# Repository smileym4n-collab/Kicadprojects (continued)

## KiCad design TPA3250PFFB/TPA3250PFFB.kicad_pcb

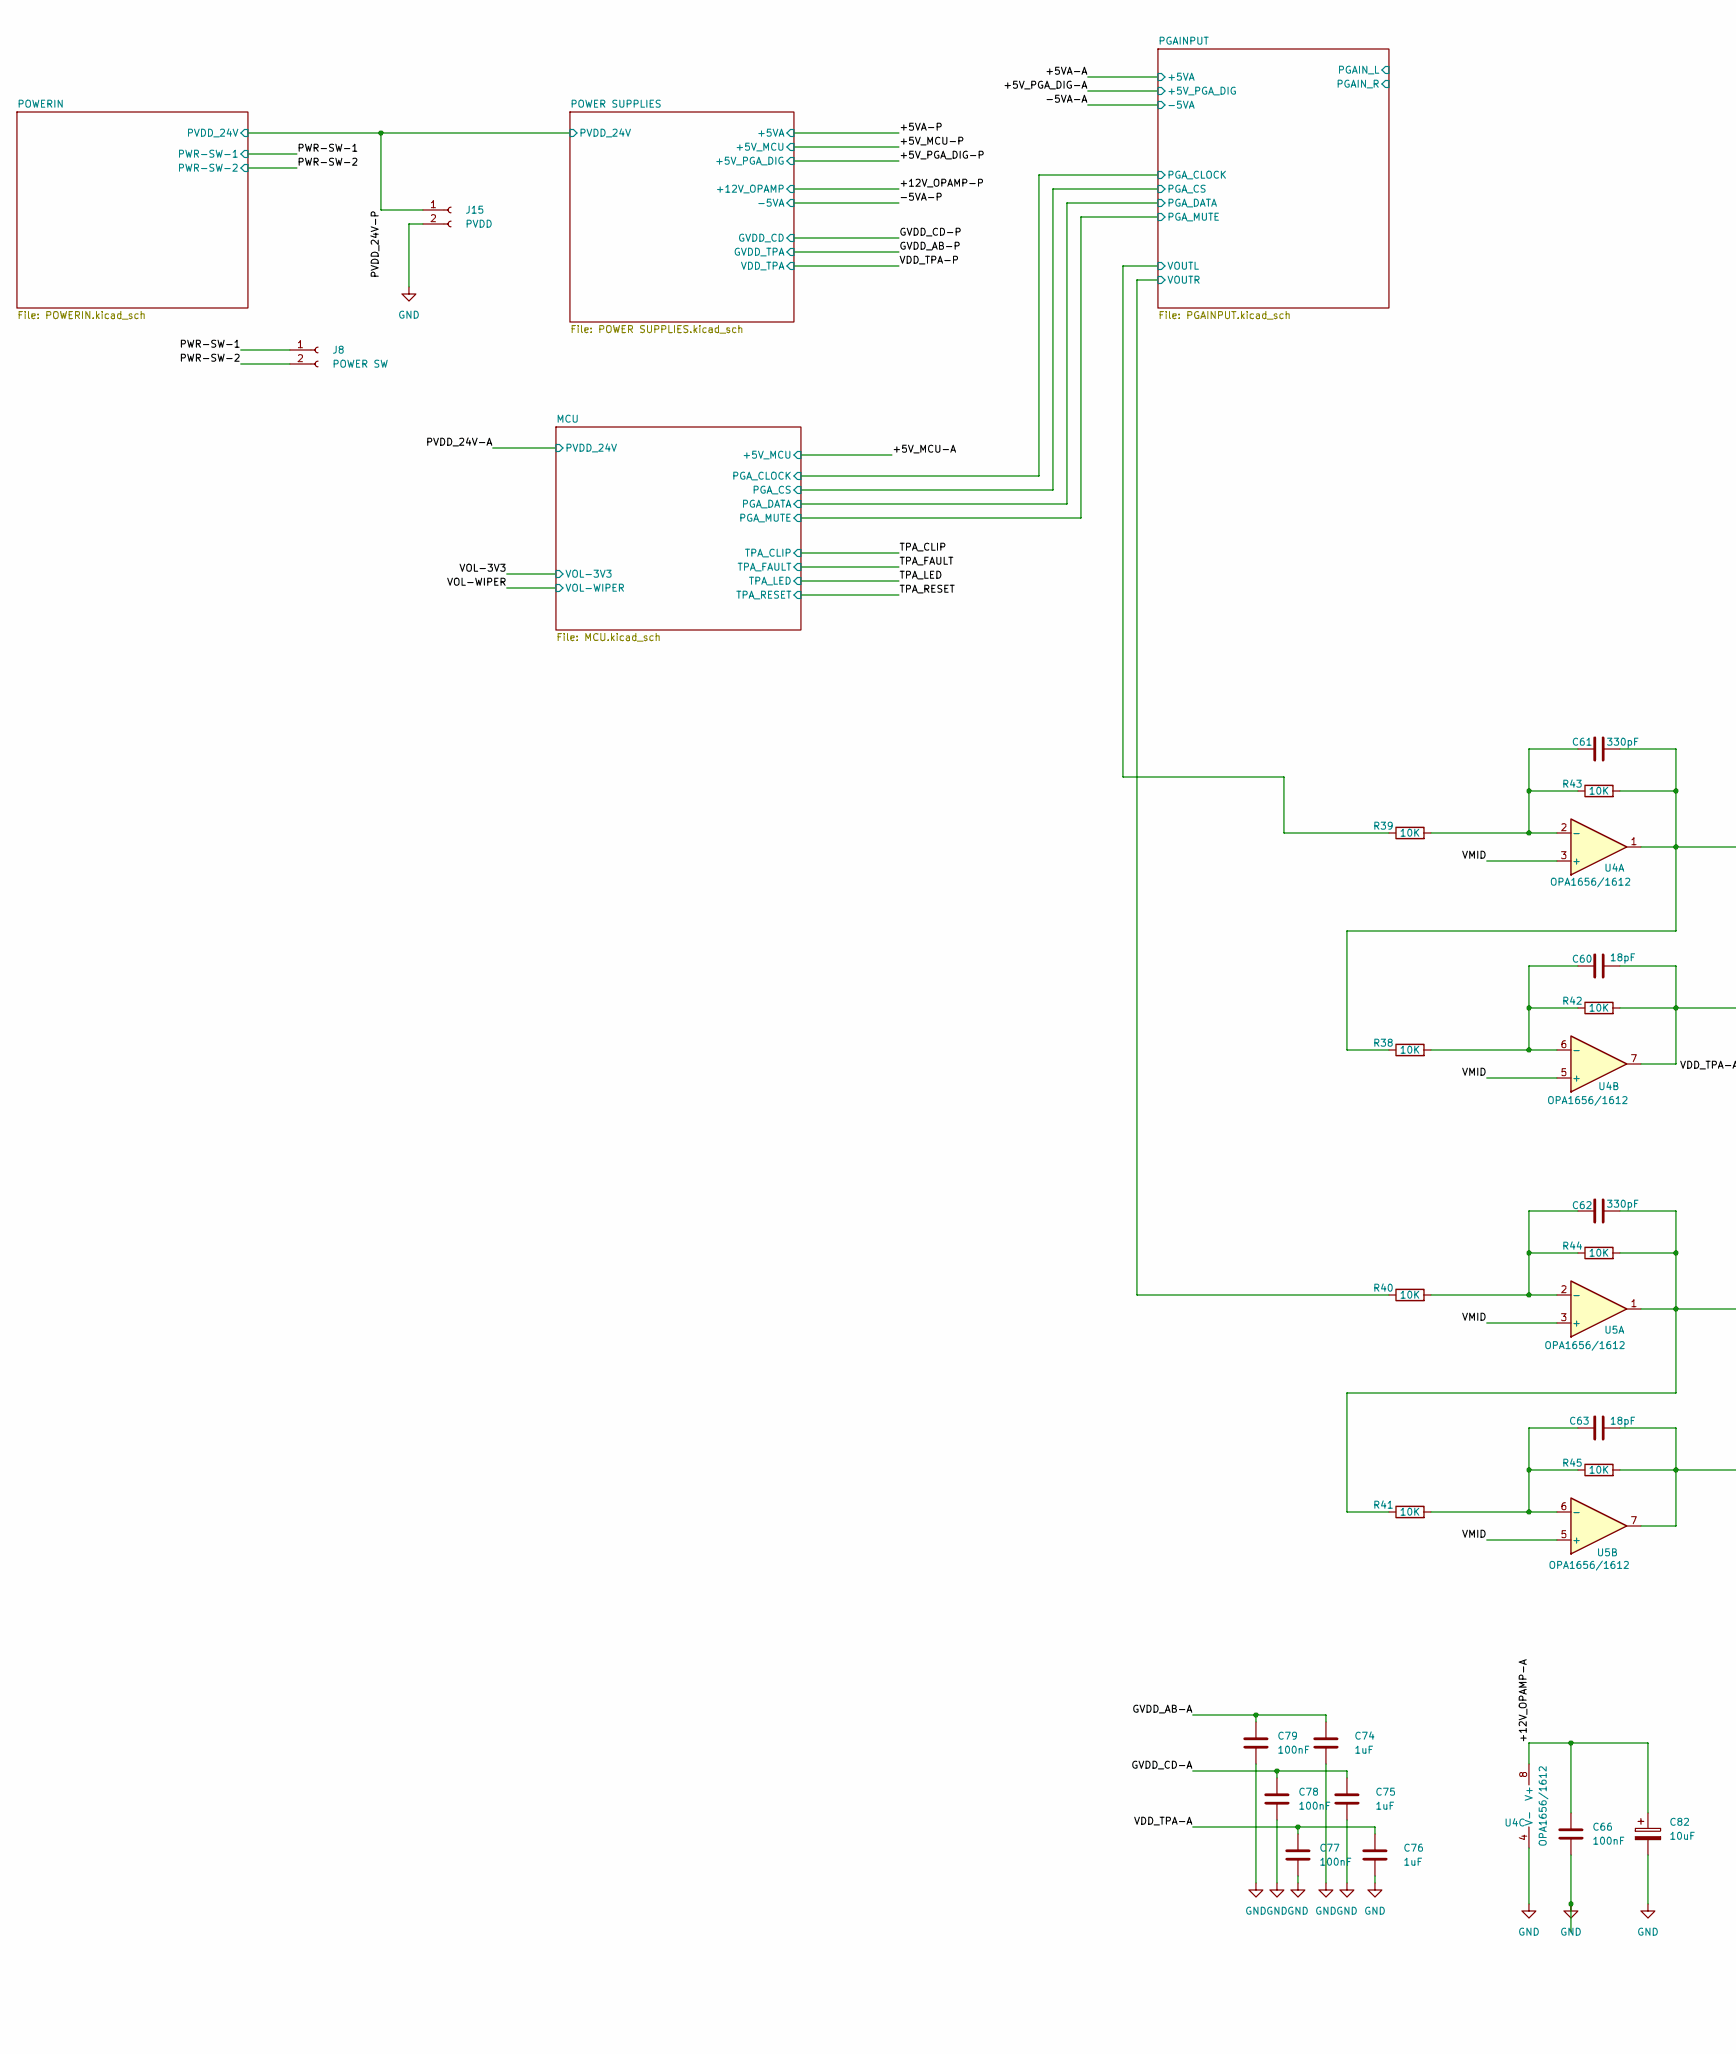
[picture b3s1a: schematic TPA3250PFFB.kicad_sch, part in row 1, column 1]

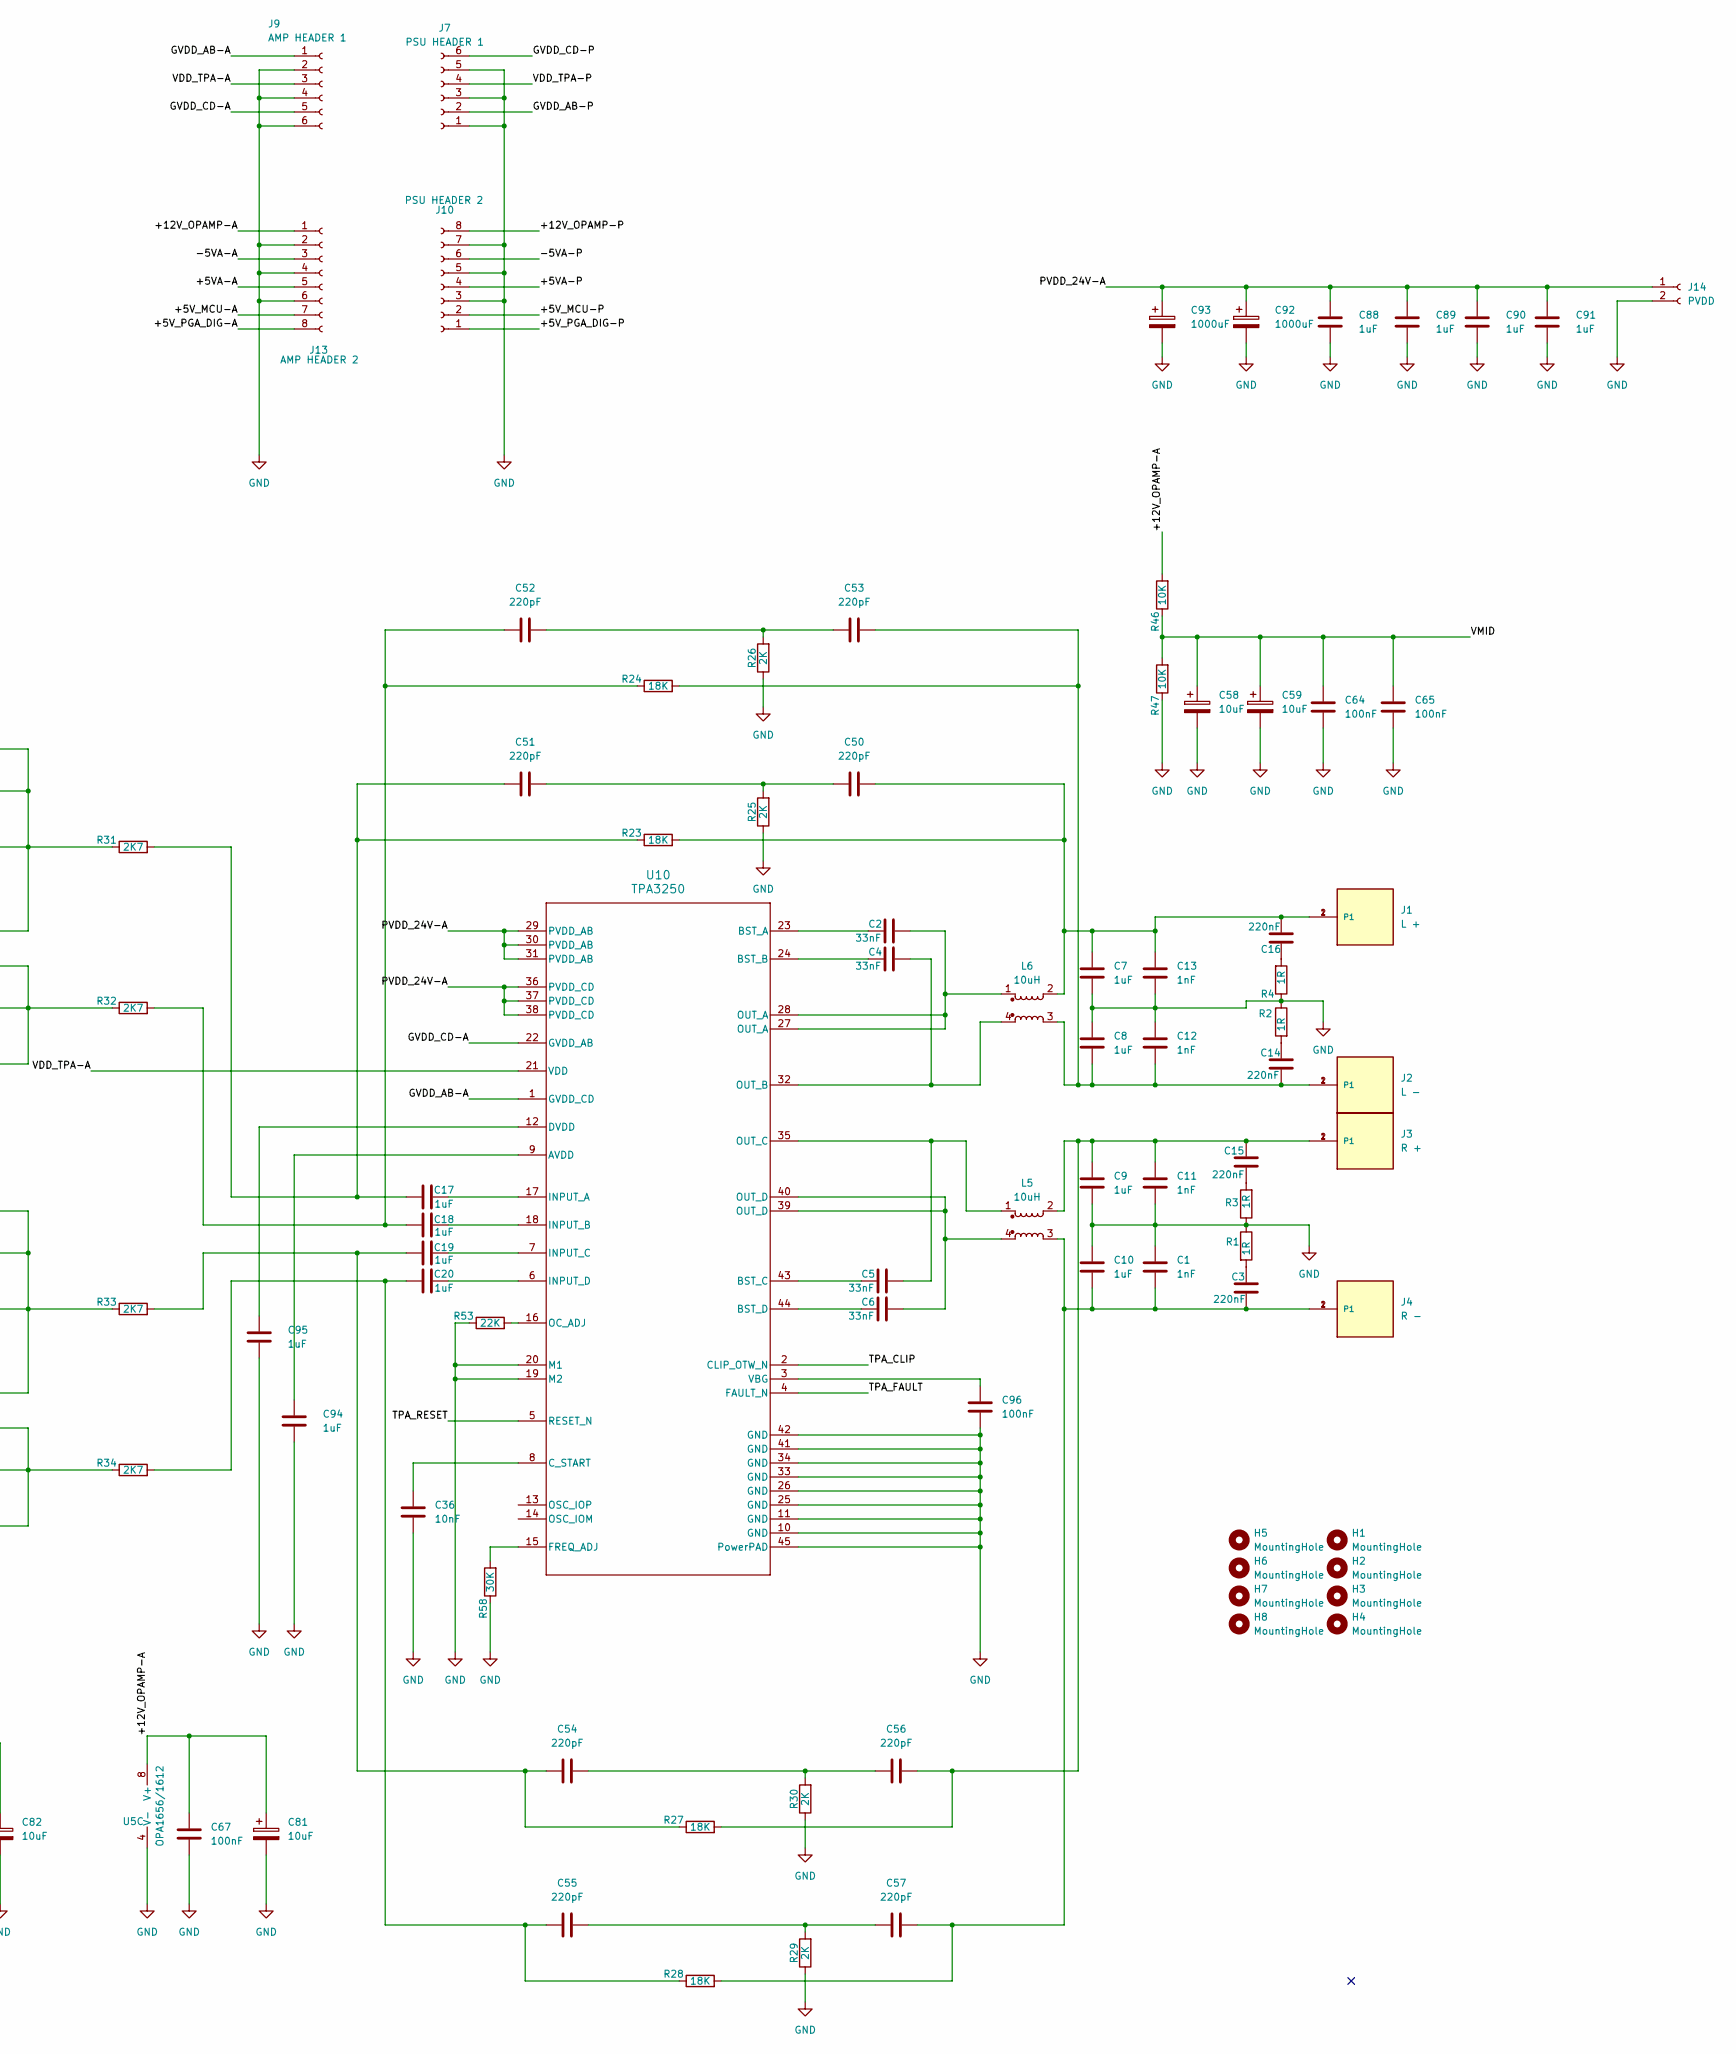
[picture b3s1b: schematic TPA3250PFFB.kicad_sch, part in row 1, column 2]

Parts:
C1, C11, C12, C13: 1nF; C_0805_2012Metric_Pad1.18x1.45mm_HandSolder
C2, C4, C5, C6: 33nF; C_0805_2012Metric_Pad1.18x1.45mm_HandSolder
C3, C14, C15, C16: 220nF; C_1206_3216Metric_Pad1.33x1.80mm_HandSolder
C7, C8, C9, C10: 1uF; C_Rect_L18.0mm_W8.0mm_P15.00mm_FKS3_FKP3
C17, C18, C19, C20: 1uF; C_Rect_L7.2mm_W5.5mm_P5.00mm_FKS2_FKP2_MKS2_MKP2
C36: 10nF; C_0805_2012Metric_Pad1.18x1.45mm_HandSolder
C50, C51, C52, C53, C54, C55, C56, C57: 220pF; C_0805_2012Metric_Pad1.18x1.45mm_HandSolder
C58, C59, C81, C82: 10uF; CP_Radial_D4.0mm_P2.00mm
C60, C63: 18pF; C_0603_1608Metric_Pad1.08x0.95mm_HandSolder
C61, C62: 330pF; C_0805_2012Metric_Pad1.18x1.45mm_HandSolder
C64, C65, C66, C67, C77, C78, C79, C96: 100nF; C_1206_3216Metric_Pad1.33x1.80mm_HandSolder
C74, C75, C76, C88, C89, C90, C91, C94, C95: 1uF; C_1206_3216Metric_Pad1.33x1.80mm_HandSolder
C92, C93: 1000uF; CP_Radial_D12.5mm_P5.00mm
H1, H2, H3, H4, H5, H6, H7, H8: MountingHole; MountingHole_4.3mm_M4
J1: L +; PART_DESCRIPTION CONN QC TAB 0.250 SOLDER
J2: L -; PART_DESCRIPTION CONN QC TAB 0.250 SOLDER
J3: R +; PART_DESCRIPTION CONN QC TAB 0.250 SOLDER
J4: R -; PART_DESCRIPTION CONN QC TAB 0.250 SOLDER
J7: PSU HEADER 1; JST_XH_B6B-XH-A_1x06_P2.50mm_Vertical
J8: POWER SW; JST_XH_B2B-XH-A_1x02_P2.50mm_Vertical
J9: AMP HEADER 1; JST_XH_B6B-XH-A_1x06_P2.50mm_Vertical
J10: PSU HEADER 2; JST_XH_B8B-XH-A_1x08_P2.50mm_Vertical
J13: AMP HEADER 2; JST_XH_B8B-XH-A_1x08_P2.50mm_Vertical
J14, J15: PVDD; Molex_KK-396_A-41791-0002_1x02_P3.96mm_Vertical
L5, L6: 10uH; CSAD0660-100M
R1, R2, R3, R4: 1R; R_2512_6332Metric_Pad1.40x3.35mm_HandSolder
R23, R24, R27, R28: 18K; R_0805_2012Metric_Pad1.20x1.40mm_HandSolder
R25, R26, R29, R30: 2K; R_0805_2012Metric_Pad1.20x1.40mm_HandSolder
R31, R32, R33, R34: 2K7; R_0805_2012Metric_Pad1.20x1.40mm_HandSolder
R38, R39, R40, R41, R42, R43, R44, R45, R46, R47: 10K; R_0805_2012Metric_Pad1.20x1.40mm_HandSolder
R53: 22K; R_0805_2012Metric_Pad1.20x1.40mm_HandSolder
R58: 30K; R_0805_2012Metric_Pad1.20x1.40mm_HandSolder
U4, U5: OPA1656/1612; SOIC-8_3.9x4.9mm_P1.27mm
U10: TPA3250

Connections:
/+5VA-A: J13.5; also elsewhere on the board
/+5VA-P: J10.4; also elsewhere on the board
/+5V_MCU-A: J13.7; also elsewhere on the board
/+5V_MCU-P: J10.2; also elsewhere on the board
/+5V_PGA_DIG-A: J13.8; also elsewhere on the board
/+5V_PGA_DIG-P: J10.1; also elsewhere on the board
/+12V_OPAMP-A: C66.1, C67.1, C81.1, C82.1, J13.1, R46.2, U4.8 (V+), U5.8 (V+)
/+12V_OPAMP-P: J10.8; also elsewhere on the board
/-5VA-A: J13.3; also elsewhere on the board
/GVDD_AB-A: C74.1, C79.1, J9.1, U10.1 (GVDD_CD)
/GVDD_AB-P: J7.2; also elsewhere on the board
/GVDD_CD-A: C75.1, C78.1, J9.5, U10.22 (GVDD_AB)
/GVDD_CD-P: J7.6; also elsewhere on the board
/PGAINPUT/VOUTL: R39.1; also elsewhere on the board
/PGAINPUT/VOUTR: R40.1; also elsewhere on the board
/PVDD_24V-A: C88.1, C89.1, C90.1, C91.1, C92.1, C93.1, J14.1, U10.29 (PVDD_AB), U10.30 (PVDD_AB), U10.31 (PVDD_AB), U10.36 (PVDD_CD), U10.37 (PVDD_CD), U10.38 (PVDD_CD); also elsewhere on the board
/PVDD_24V-P: J15.1; also elsewhere on the board
/PWR-SW-1: J8.1; also elsewhere on the board
/TPA_CLIP: U10.2 (CLIP_OTW_N); also elsewhere on the board
/TPA_FAULT: U10.4 (FAULT_N); also elsewhere on the board
/TPA_RESET: U10.5 (RESET_N); also elsewhere on the board
/VDD_TPA-A: C76.1, C77.1, J9.3, U10.21 (VDD)
/VDD_TPA-P: J7.4; also elsewhere on the board
/VMID: C58.1, C59.1, C64.1, C65.1, R46.1, R47.2, U4.3 (+), U4.5 (+), U5.3 (+), U5.5 (+)
unnamed: C2.2, L6.1, U10.27 (OUT_A), U10.28 (OUT_A)
unnamed: C3.1, R1.2
unnamed: C6.2, L5.4, U10.39 (OUT_D), U10.40 (OUT_D)
unnamed: C14.1, R2.2
unnamed: C15.1, R3.2
unnamed: C16.1, R4.2
unnamed: C17.1, C51.1, R23.1, R31.2
unnamed: C18.1, C52.1, R24.1, R32.2
unnamed: C19.1, C54.1, R27.1, R33.2
unnamed: C20.1, C55.1, R28.1, R34.2
unnamed: C50.1, C51.2, R25.2
unnamed: C52.2, C53.1, R26.2
unnamed: C54.2, C56.1, R30.2
unnamed: C55.2, C57.1, R29.2
unnamed: C60.2, R32.1, R42.2, U4.7
unnamed: C61.2, R31.1, R38.1, R43.2, U4.1
unnamed: C62.2, R33.1, R41.1, R44.2, U5.1
unnamed: C63.2, R34.1, R45.2, U5.7
unnamed 66: C7.2, C13.1, C16.2, C50.2, J1.1, J1.2, L6.2, R23.2; also elsewhere on the board
unnamed 67: C8.1, C12.2, C14.2, C53.2, J2.1, J2.2, L6.3, R24.2; also elsewhere on the board
unnamed 68: C9.2, C11.1, C15.2, C56.2, J3.1, J3.2, L5.2, R27.2; also elsewhere on the board
unnamed 69: C1.2, C3.2, C10.1, C57.2, J4.1, J4.2, L5.3, R28.2; also elsewhere on the board
unnamed: C61.1, R39.2, R43.1, U4.2 (-)
unnamed: C60.1, R38.2, R42.1, U4.6 (-)
unnamed: C62.1, R40.2, R44.1, U5.2 (-)
unnamed: C63.1, R41.2, R45.1, U5.6 (-)
unnamed: C94.1, U10.9 (AVDD)
unnamed: C2.1, U10.23 (BST_A)
unnamed: C4.1, U10.24 (BST_B)
unnamed: C5.1, U10.43 (BST_C)
unnamed: C6.1, U10.44 (BST_D)
unnamed: C36.1, U10.8 (C_START)
unnamed: C95.1, U10.12 (DVDD)
unnamed: R58.2, U10.15 (FREQ_ADJ)
unnamed: C19.2, U10.7 (INPUT_C)
unnamed: C20.2, U10.6 (INPUT_D)
unnamed: R53.2, U10.16 (OC_ADJ)
unnamed: C4.2, L6.4, U10.32 (OUT_B)
unnamed: C5.2, L5.1, U10.35 (OUT_C)
unnamed: C96.1, U10.3 (VBG)

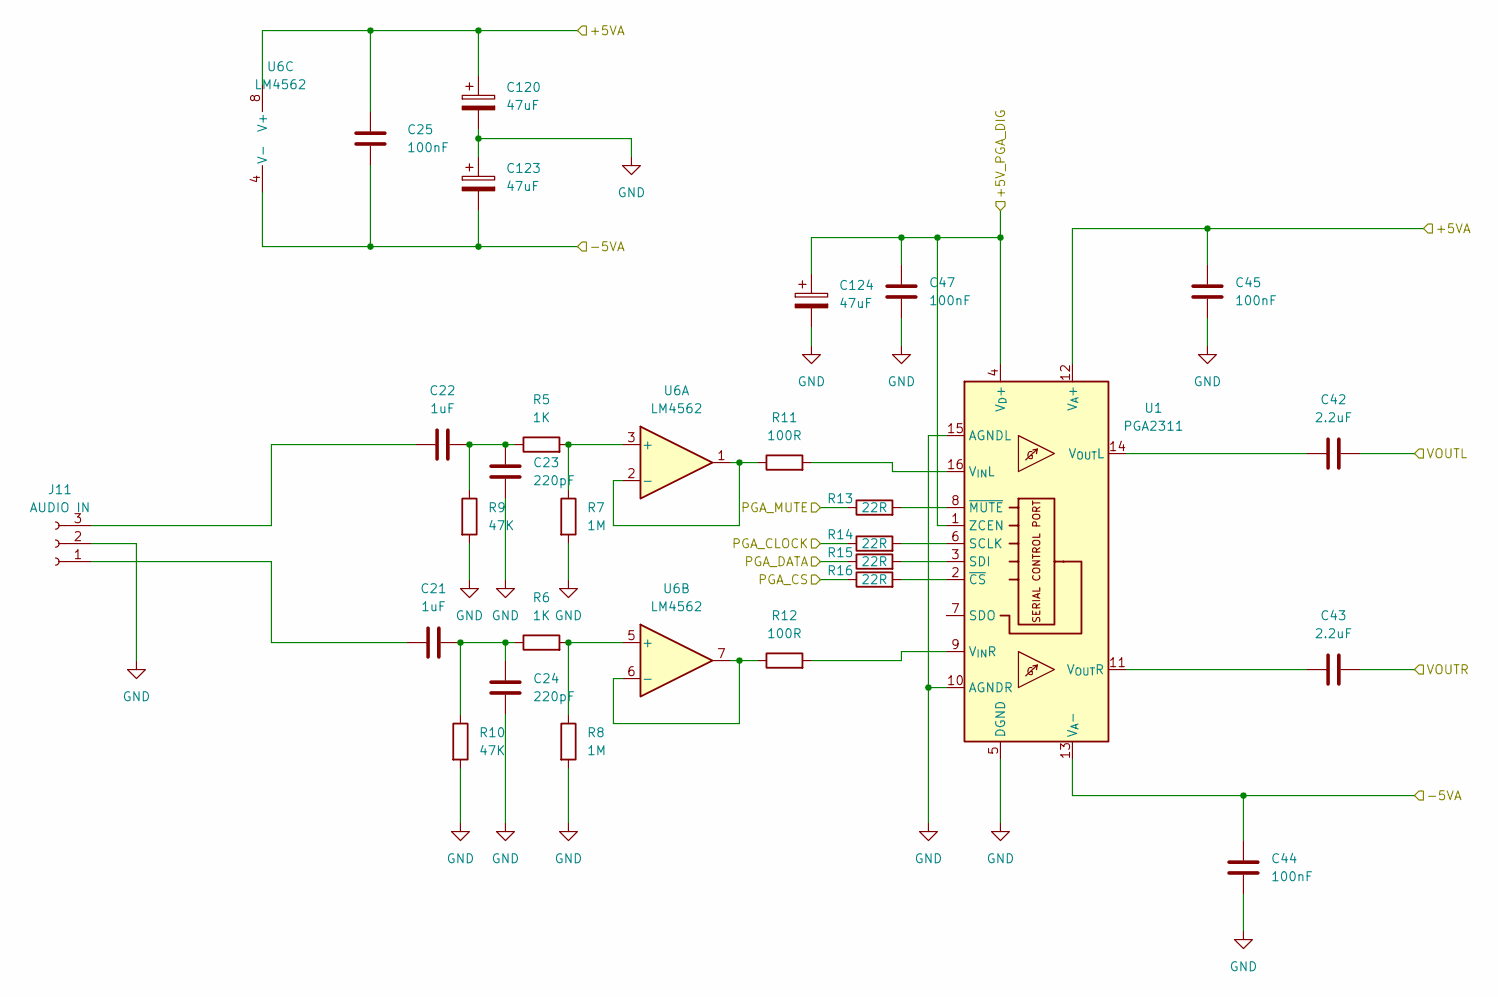
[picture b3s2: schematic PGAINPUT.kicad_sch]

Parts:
C21, C22: 1uF; C_Rect_L7.2mm_W5.5mm_P5.00mm_FKS2_FKP2_MKS2_MKP2
C23, C24: 220pF; C_0805_2012Metric_Pad1.18x1.45mm_HandSolder
C25, C44, C45, C47: 100nF; C_1206_3216Metric_Pad1.33x1.80mm_HandSolder
C42, C43: 2.2uF; C_Rect_L7.2mm_W7.2mm_P5.00mm
C120, C123, C124: 47uF; CP_Radial_D5.0mm_P2.50mm
J11: AUDIO IN; JST_XH_B3B-XH-A_1x03_P2.50mm_Vertical
R5, R6: 1K; R_0805_2012Metric_Pad1.20x1.40mm_HandSolder
R7, R8: 1M; R_0805_2012Metric_Pad1.20x1.40mm_HandSolder
R9, R10: 47K; R_0805_2012Metric_Pad1.20x1.40mm_HandSolder
R11, R12: 100R; R_0805_2012Metric_Pad1.20x1.40mm_HandSolder
R13, R14, R15, R16: 22R; R_0805_2012Metric_Pad1.20x1.40mm_HandSolder
U1: PGA2311; DIP-16_W7.62mm_Socket
U6: LM4562; DIP-8_W7.62mm_Socket

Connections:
/+5VA-A: C25.1, C45.1, C120.1, U1.12 (V_{A}+), U6.8 (V+); also elsewhere on the board
/+5V_PGA_DIG-A: C47.1, C124.1, U1.1 (ZCEN), U1.4 (V_{D}+); also elsewhere on the board
/-5VA-A: C25.2, C44.1, C123.2, U1.13 (V_{A}-), U6.4 (V-); also elsewhere on the board
/MCU/PGA_CLOCK: R14.1; also elsewhere on the board
/MCU/PGA_CS: R16.1; also elsewhere on the board
/MCU/PGA_DATA: R15.1; also elsewhere on the board
/MCU/PGA_MUTE: R13.1; also elsewhere on the board
/PGAINPUT/VOUTL: C42.2; also elsewhere on the board
/PGAINPUT/VOUTR: C43.2; also elsewhere on the board
unnamed: C21.2, C24.1, R6.1, R10.1
unnamed: C22.2, C23.1, R5.1, R9.1
unnamed: C21.1, J11.1
unnamed: C22.1, J11.3
unnamed: R14.2, U1.6 (SCLK)
unnamed: R15.2, U1.3 (SDI)
unnamed: R11.2, U1.16 (V_{IN}L)
unnamed: R12.2, U1.9 (V_{IN}R)
unnamed: C42.1, U1.14 (V_{OUT}L)
unnamed: C43.1, U1.11 (V_{OUT}R)
unnamed: R16.2, U1.2 (~CS)
unnamed: R13.2, U1.8 (~MUTE)
unnamed: R5.2, R7.1, U6.3 (+)
unnamed: R11.1, U6.1, U6.2 (-)
unnamed: R6.2, R8.1, U6.5 (+)
unnamed: R12.1, U6.6 (-), U6.7

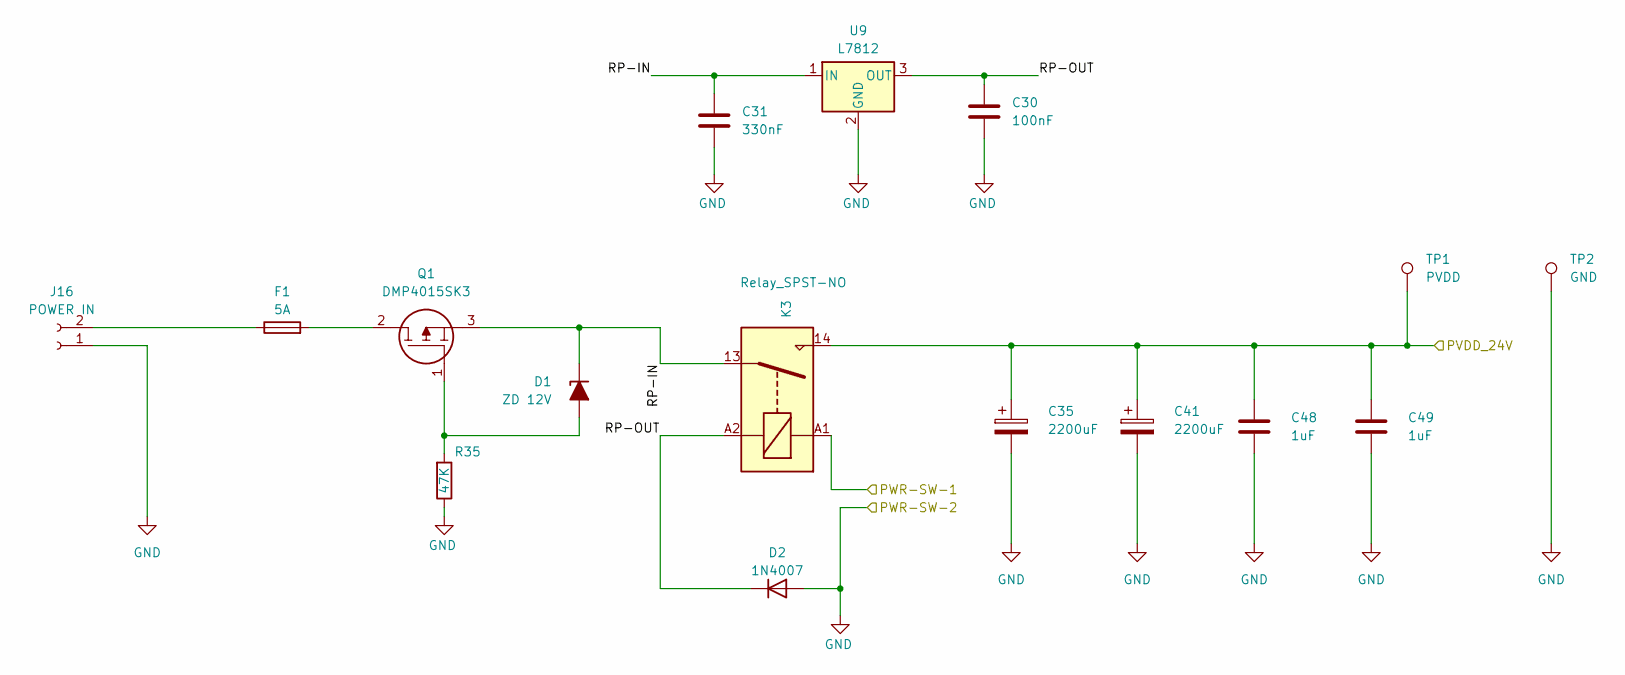
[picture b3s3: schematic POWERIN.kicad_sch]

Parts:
C30: 100nF; C_Disc_D3.8mm_W2.6mm_P2.50mm
C31: 330nF; C_Disc_D3.8mm_W2.6mm_P2.50mm
C35, C41: 2200uF; CP_Radial_D16.0mm_P7.50mm
C48, C49: 1uF; C_1206_3216Metric_Pad1.33x1.80mm_HandSolder
D1: ZD 12V; D_DO-201AD_P12.70mm_Horizontal
D2: 1N4007; D_DO-41_SOD81_P10.16mm_Horizontal
F1: 5A; Fuse_Littelfuse_395Series
J16: POWER IN; Molex_KK-396_A-41791-0002_1x02_P3.96mm_Vertical
K3: Relay_SPST-NO; Relay_SPST_Omron_G2RL-1A
Q1: DMP4015SK3; DMP4015SK313; Manufacturer_Part_Number DMP4015SK3-13
R35: 47K; R_0805_2012Metric_Pad1.20x1.40mm_HandSolder
TP1: PVDD; TestPoint_Pad_D2.0mm
TP2: GND; TestPoint_Pad_D2.0mm
U9: L7812; TO-220-3_Vertical

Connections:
/POWERIN/RP-IN: C31.1, D1.1 (K), K3.13, Q1.3, U9.1 (IN)
/POWERIN/RP-OUT: C30.1, D2.1 (K), K3.A2, U9.3 (OUT)
/PVDD_24V-P: C35.1, C41.1, C48.1, C49.1, K3.14, TP1.1 (1_1); also elsewhere on the board
/PWR-SW-1: K3.A1; also elsewhere on the board
unnamed: D1.2 (A), Q1.1, R35.2
unnamed: F1.2, Q1.2
unnamed: F1.1, J16.2

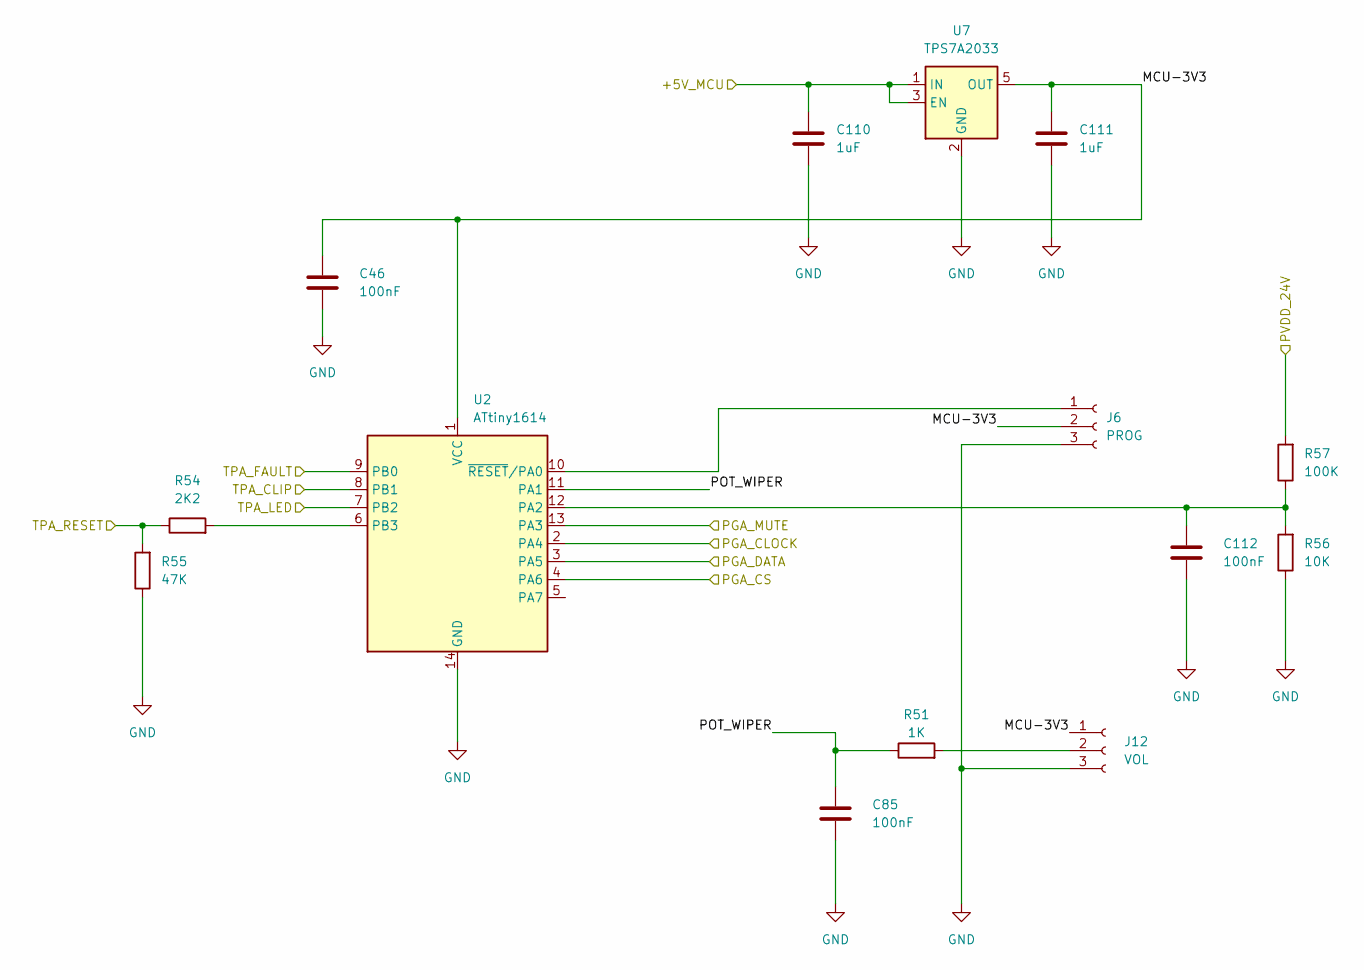
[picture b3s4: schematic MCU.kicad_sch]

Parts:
C46, C85, C112: 100nF; C_1206_3216Metric_Pad1.33x1.80mm_HandSolder
C110, C111: 1uF; C_1206_3216Metric_Pad1.33x1.80mm_HandSolder
J6: PROG; JST_XH_B3B-XH-A_1x03_P2.50mm_Vertical
J12: VOL; JST_XH_B3B-XH-A_1x03_P2.50mm_Vertical
R51: 1K; R_0805_2012Metric_Pad1.20x1.40mm_HandSolder
R54: 2K2; R_0805_2012Metric_Pad1.20x1.40mm_HandSolder
R55: 47K; R_0805_2012Metric_Pad1.20x1.40mm_HandSolder
R56: 10K; R_0805_2012Metric_Pad1.20x1.40mm_HandSolder
R57: 100K; R_0805_2012Metric_Pad1.20x1.40mm_HandSolder
U2: ATtiny1614; SOIC-14_3.9x8.7mm_P1.27mm
U7: TPS7A2033; SOT-23-5

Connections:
/+5V_MCU-A: C110.1, U7.1 (IN), U7.3 (EN); also elsewhere on the board
/MCU/MCU-3V3: C46.1, C111.1, J6.2, J12.1, U2.1 (VCC), U7.5 (OUT)
/MCU/PGA_CLOCK: U2.2 (PA4); also elsewhere on the board
/MCU/PGA_CS: U2.4 (PA6); also elsewhere on the board
/MCU/PGA_DATA: U2.3 (PA5); also elsewhere on the board
/MCU/PGA_MUTE: U2.13 (PA3); also elsewhere on the board
/MCU/POT_WIPER: C85.1, R51.1, U2.11 (PA1)
/PVDD_24V-A: R57.2; also elsewhere on the board
/TPA_CLIP: U2.8 (PB1); also elsewhere on the board
/TPA_FAULT: U2.9 (PB0); also elsewhere on the board
/TPA_LED: U2.7 (PB2)
/TPA_RESET: R54.1, R55.2; also elsewhere on the board
unnamed: J6.1, U2.10 (~RESET/PA0)
unnamed: J12.2, R51.2
unnamed: C112.1, R56.2, R57.1, U2.12 (PA2)
unnamed: R54.2, U2.6 (PB3)

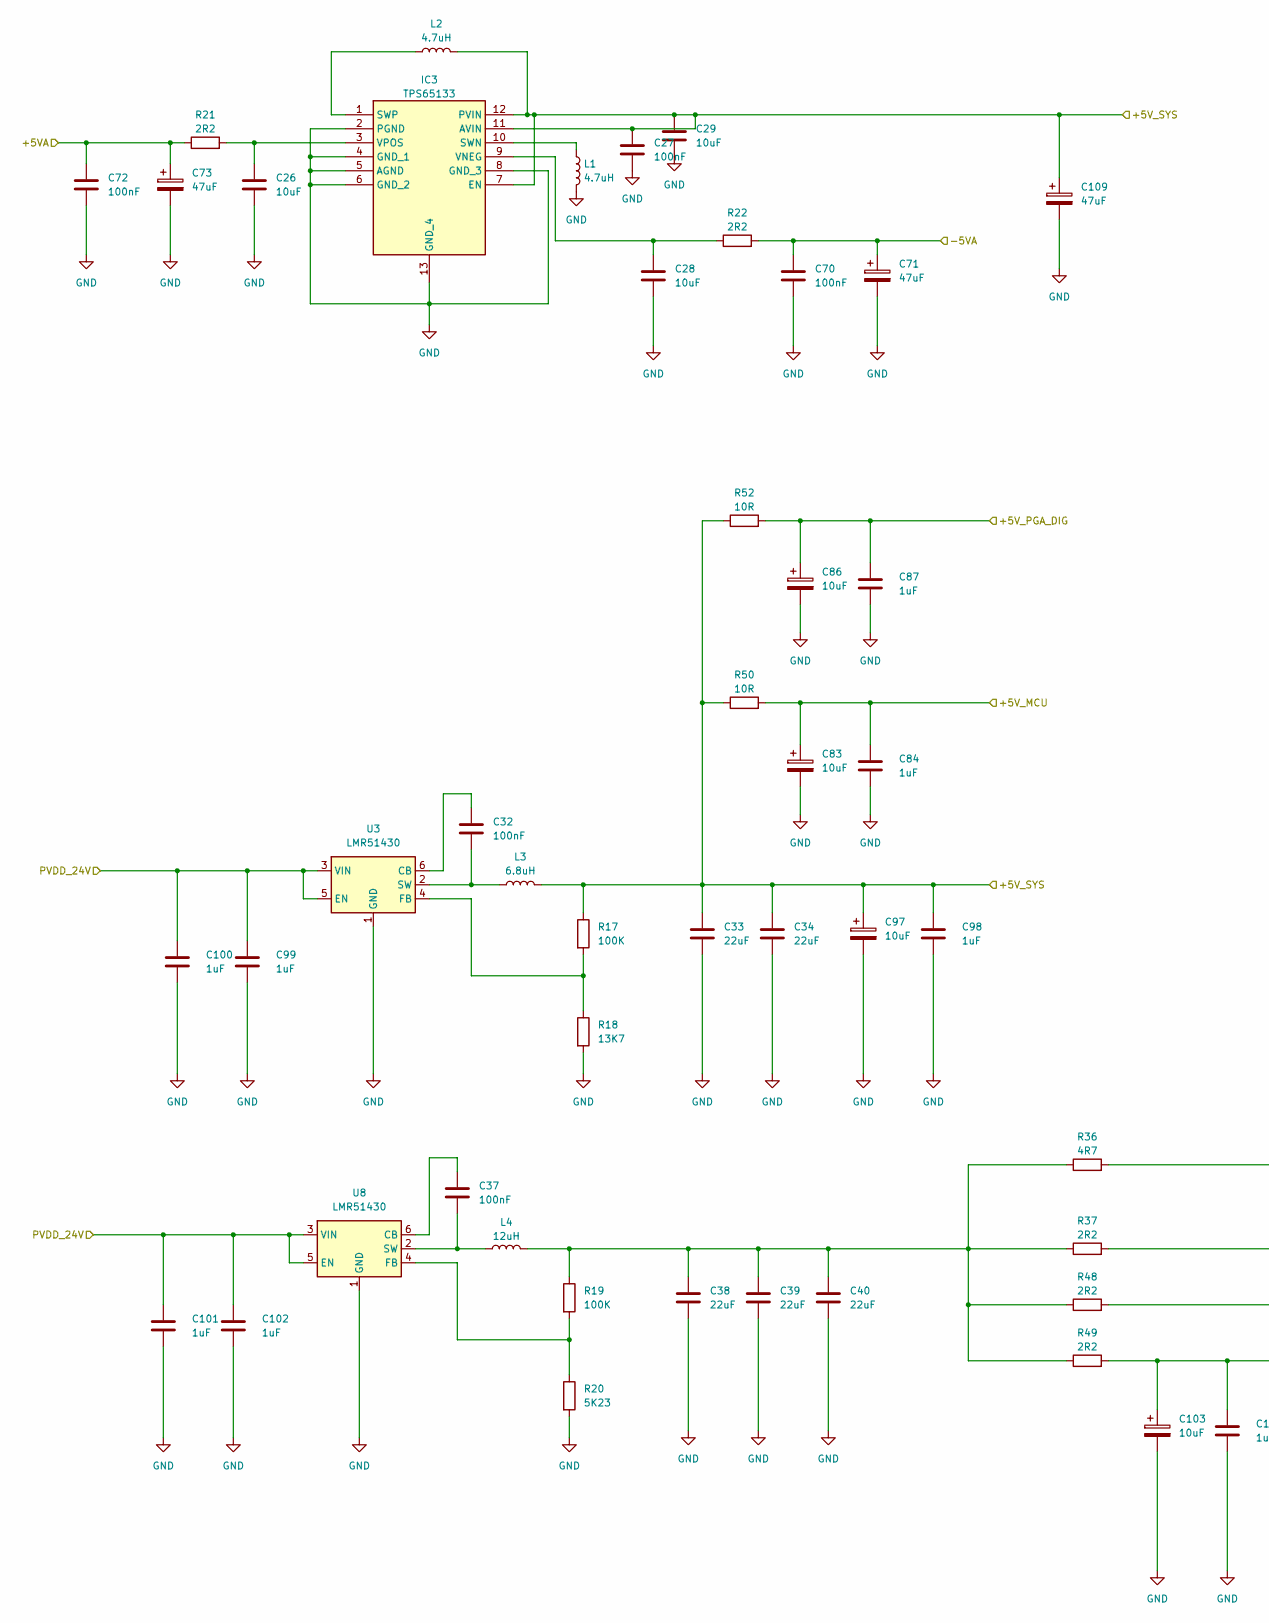
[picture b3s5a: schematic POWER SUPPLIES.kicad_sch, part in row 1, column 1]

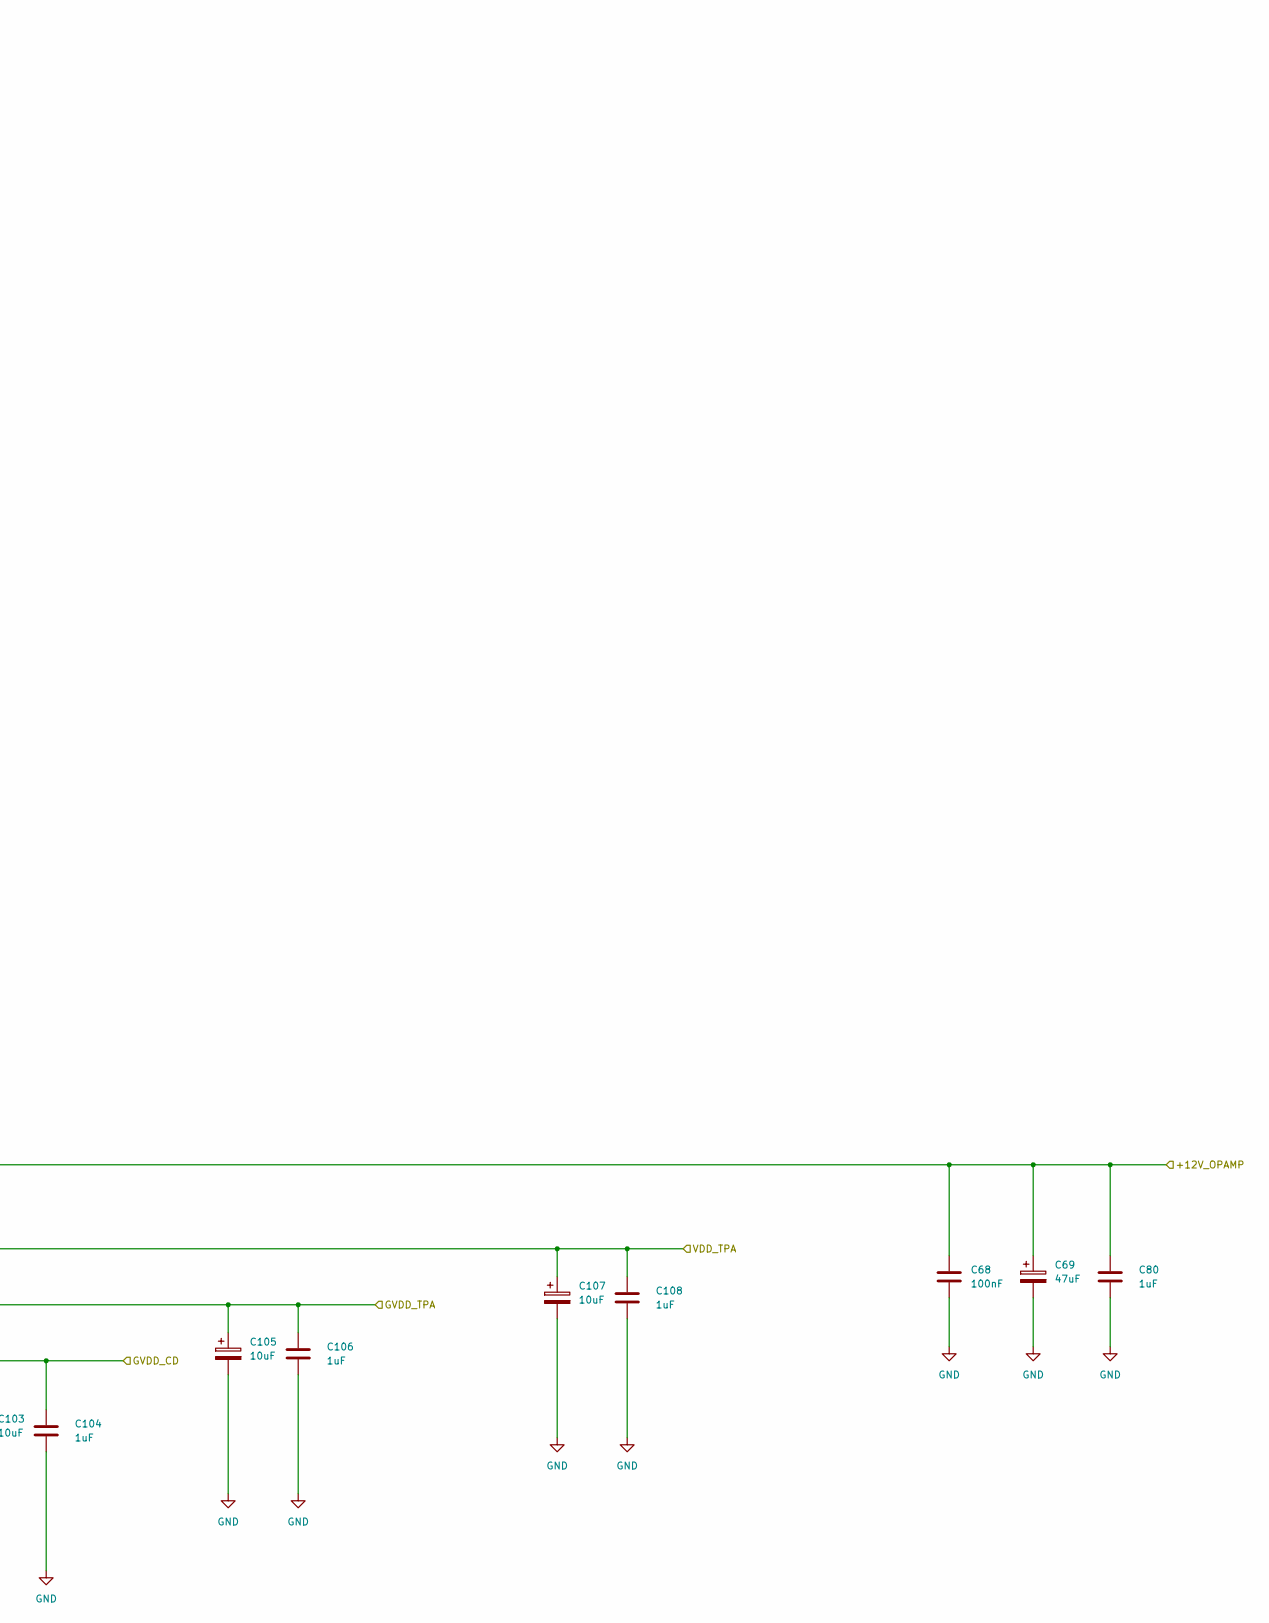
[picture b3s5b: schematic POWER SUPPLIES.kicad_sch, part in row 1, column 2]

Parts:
C26, C28, C29: 10uF; C_0805_2012Metric_Pad1.18x1.45mm_HandSolder
C27, C32, C37, C68, C70, C72: 100nF; C_1206_3216Metric_Pad1.33x1.80mm_HandSolder
C33, C34, C38, C39, C40: 22uF; C_1206_3216Metric_Pad1.33x1.80mm_HandSolder
C69, C71, C73, C109: 47uF; CP_Radial_D5.0mm_P2.50mm
C80, C84, C87, C98, C99, C100, C101, C102, C104, C106, C108: 1uF; C_1206_3216Metric_Pad1.33x1.80mm_HandSolder
C83, C86, C97, C103, C105, C107: 10uF; CP_Radial_D4.0mm_P2.00mm
IC3: TPS65133; SON45P300X300X80-13N-D; Mouser Part Number 595-TPS65133DPDR
L1, L2: 4.7uH; L_1008_2520Metric_Pad1.43x2.20mm_HandSolder
L3: 6.8uH; SRP6030WA-6R8M
L4: 12uH; SRR1050A-120Y
R17, R19: 100K; R_0805_2012Metric_Pad1.20x1.40mm_HandSolder
R18: 13K7; R_0805_2012Metric_Pad1.20x1.40mm_HandSolder
R20: 5K23; R_0805_2012Metric_Pad1.20x1.40mm_HandSolder
R21, R22, R37, R48, R49: 2R2; R_0805_2012Metric_Pad1.20x1.40mm_HandSolder
R36: 4R7; R_0805_2012Metric_Pad1.20x1.40mm_HandSolder
R50, R52: 10R; R_0805_2012Metric_Pad1.20x1.40mm_HandSolder
U3, U8: LMR51430; SOT-23-6

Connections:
/+5VA-P: C72.1, C73.1, R21.1; also elsewhere on the board
/+5V_MCU-P: C83.1, C84.1, R50.2; also elsewhere on the board
/+5V_PGA_DIG-P: C86.1, C87.1, R52.2; also elsewhere on the board
/+12V_OPAMP-P: C68.1, C69.1, C80.1, R36.2; also elsewhere on the board
/GVDD_AB-P: C105.1, C106.1, R48.2; also elsewhere on the board
/GVDD_CD-P: C103.1, C104.1, R49.2; also elsewhere on the board
/POWER SUPPLIES/+5V_SYS: C27.1, C29.1, C33.1, C34.1, C97.1, C98.1, C109.1, IC3.7 (EN), IC3.11 (AVIN), IC3.12 (PVIN), L2.2, L3.2, R17.1, R50.1, R52.1
/PVDD_24V-P: C99.1, C100.1, C101.1, C102.1, U3.3 (VIN), U3.5 (EN), U8.3 (VIN), U8.5 (EN); also elsewhere on the board
/VDD_TPA-P: C107.1, C108.1, R37.2; also elsewhere on the board
unnamed: C38.1, C39.1, C40.1, L4.2, R19.1, R36.1, R37.1, R48.1, R49.1
unnamed: IC3.10 (SWN), L1.1
unnamed: IC3.1 (SWP), L2.1
unnamed: C28.1, IC3.9 (VNEG), R22.1
unnamed: C26.1, IC3.3 (VPOS), R21.2
unnamed: C32.1, U3.6 (CB)
unnamed: R17.2, R18.1, U3.4 (FB)
unnamed: C32.2, L3.1, U3.2 (SW)
unnamed: C37.1, U8.6 (CB)
unnamed: R19.2, R20.1, U8.4 (FB)
unnamed: C37.2, L4.1, U8.2 (SW)

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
